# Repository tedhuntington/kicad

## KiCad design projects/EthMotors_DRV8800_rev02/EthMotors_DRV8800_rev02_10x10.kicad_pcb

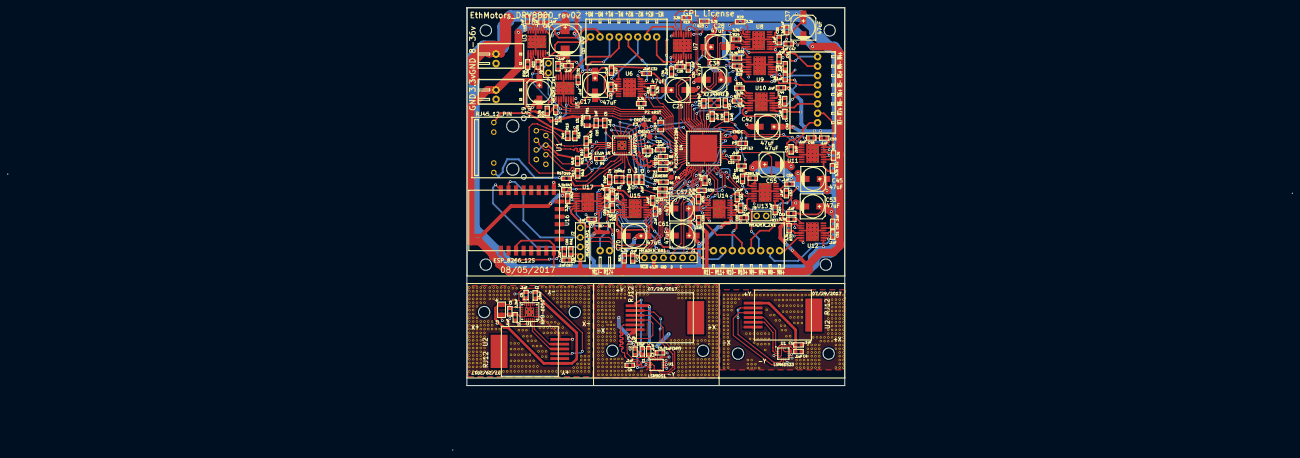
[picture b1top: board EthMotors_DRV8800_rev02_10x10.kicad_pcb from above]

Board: 2 copper layers, 100.0 x 100.0 mm, 178 parts (0 on the bottom side), 169 nets.

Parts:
C1, C1#4, C2#3, C3#3, C4#2, C4#3, C4#4, C5, C5#2, C6, C7, C8, C10, C11, C12, C16, C18, C21, C22, C23, C24, C26, C27, C29, C30, C31, C32, C33, C34, C35, C36, C39, C40, C41, C43, C44, C46, C47, C48, C49, C50, C51, C52, C54, C56, C58, C59, C60, C62, C63, C64, C65, C66, C67, C68, C69, C71, C72: .1uF; TED_SM0603_C
C1#2: 10nF; TED_SM0603_C
C1#3: 10uF; TED_SM0603_C
C2, C15: 1uF; TED_SM0603_C
C2#2: 2.2nF; TED_SM0603_C
C3, C4: 10pF; TED_SM0603_C
C3#2: 4.7uF; TED_SM3216_1206_ELEC_C
C5#3: .01uF(16V); TED_SM0603_C
C9, C17, C25, C28, C37, C38, C42, C45, C53, C55, C57, C61, C70: 47uF; c_elec_6.3x7.7
C13: 47uF; TED_c_elec_8x10
C14: 10uF (low ESR 1ohm); TED_SM0805_C
C19, C20: 9pF; TED_SM0603_C
FB1: 500mA; TED_SM0805_C
H1, H1#2, H1#3, H1#4, H2, H2#2, H2#3, H2#4, H3, H4: HOLE; TED_Hole_3mm
J1: HEADER_6X1; TED_HEADER_6x1
J2: HEADER_4X1; TED_HEADER_4x1
J3, J10: Logic DC_2.1MM; TED_TERMINAL_SPRING_2.54MM_2PIN_1989748
J4, J5, J7: TERMINAL_8X1; TED_TERMINAL_SPRING_2.54MM_8PIN_1989803
J6: Terminal_2x1; TED_TERMINAL_SPRING_2.54MM_2PIN_1989748
J8, J9: HEADER_2X1; TED_HEADER_2x1
P1: EMDIO; TED_TEST_PAD
P2: nRST; TED_TEST_PAD
P3: EREFCLK; TED_TEST_PAD
P4: ERXERR; TED_TEST_PAD
P5: EMDC; TED_TEST_PAD
R1, R2, R3, R6, R7, R8: 33; TED_SM0603_R
R4: 12.1k 1%; TED_SM0603_R
R5: 10; TED_SM0603_R
R9, R10, R11, R12: 49.9; TED_SM0603_R
R13, R15: 249; TED_SM0603_R
R14: 4.7k; TED_SM0603_R
R16: 10k 1%; TED_SM0603_R
R17, R18, R19, R20, R21, R22, R23, R24, R25, R26, R27, R28, R29, R30, R31, R32, R33, R34, R35, R36, R37, R38, R39, R40, R42, R43: 3.3k; TED_SM0603_R
R41: 10k; TED_SM0603_R
U1: RJ45_12_PIN; TED_RJ45_12pin
U1#2: MPU-6050; TED_QFN24+1_NO_PASTE
U1#3: LSM9DS1; LGA-24
U1#4: LSM6DS33; LGA-16
U2: LAN8720A; TED_QFN24+1
U2#2, U2#3, U2#4: RJ12; TED_RJ12_855135002
U3, U5, U6, U7, U8, U9, U10, U11, U12, U13, U14, U15, U17: DRV8800_PWP; TSSOP_16+1H
U4: PIC32MX664F128H; TED_QFN64+1
U16: ESP_8266_12S
X1: 25Mhz; TED_crystal_FA-20H
X2: 24MHz; crystal_TSX3225

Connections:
AVDD: C5.1, C15.1, FB1.2, R9.1, R10.1, R11.1, R12.1, U1.4, U1.5, U2.1, U2.19
ECRSDV: R8.2, U4.62
EMDC: P5.1, U2.13, U4.30
EMDIO: P1.1, U2.12, U4.49
EREFCLK: P3.1, U2.14, U4.63
ERXD0: R7.2, U4.61
ERXD1: R6.2, U4.60
ERXERR: P4.1, U2.10, U4.64
ETXD0: R2.2, U4.2
ETXD1: R3.2, U4.3
ETXEN: R1.2, U4.1
GND: C1.2, C1#2.2, C1#3.2, C1#4.2, C2.2, C2#2.2, C2#3.2, C3.2, C3#2.2, C3#3.2, C4.1, C4#2.2, C4#3.2, C4#4.2, C5.2, C5#2.2, C5#3.2, C7.2, C8.2, C9.2, C10.2, C11.2, C12.2, C13.2, C14.2, C15.2, C16.2, C17.2, C18.2, C19.2, C20.2, C21.2, C24.2, C25.2, C28.2, C31.2, C32.2, C34.2, C37.2, C38.2, C42.2, C45.2, C47.2, C48.2, C49.2, C50.2, C53.2, C55.2, C57.2, C61.2, C63.2, C64.2, C65.2, C66.2, C67.2, C68.2, C70.2, C72.2, J1.3, J2.4, J3.2, J9.1, J9.2, J10.2, R4.2, R16.2, U1.8, U1.10, U1.11, U1#2.1, U1#2.9, U1#2.11, U1#2.18, U1#2.25, U1#3.5, U1#3.6, U1#3.14, U1#3.15, U1#3.16, U1#3.17, U1#3.18, U1#3.19, U1#3.20, U1#4.4, U1#4.8, U1#4.9, U1#4.10, U1#4.11, U1#4.12, U1#4.13, U1#4.15, U2.25, U2#2.1, U2#3.1, U2#4.1, U3.4, U3.8, U3.13, U3.17, U4.9, U4.20, U4.25, U4.41, U4.65, U5.4, U5.8, U5.13, U5.17, U6.4, U6.8, U6.13, U6.17, U7.4, U7.8, U7.13, U7.17, U8.4, U8.8, U8.13, U8.17, U9.4, U9.8, U9.13, U9.17, U10.4, U10.8, U10.13, U10.17, U11.4, U11.8, U11.13, U11.17, U12.4, U12.8, U12.13, U12.17, U13.4, U13.8, U13.13, U13.17, U14.4, U14.8, U14.13, U14.17, U15.4, U15.8, U15.13, U15.17, U16.15, U17.4, U17.8, U17.13, U17.17, X1.2, X1.4, X2.2, X2.4
GreenLED: R15.1, U1.9
INT: U1#2.12, U2#2.4
INT1: U1#3.11, U1#4.7, U2#3.4, U2#4.4
INT2: U1#3.12, U1#4.6, U2#3.5, U2#4.5
M0+: J7.8, U3.7
M0-: J7.7, U3.10
M1+: J7.6, U5.7
M1-: J7.5, U5.10
M2+: J7.4, U6.7
M2-: J7.3, U6.10
M3+: J7.2, U7.7
M3-: J7.1, U7.10
M4+: J4.8, U8.7
M4-: J4.7, U8.10
M5+: J4.6, U9.7
M5-: J4.5, U9.10
M6+: J4.4, U10.7
M6-: J4.3, U10.10
M7+: J4.2, U11.7
M7-: J4.1, U11.10
M8+: J5.8, U12.7
M8-: J5.7, U12.10
M9+: J5.6, U13.7
M9-: J5.5, U13.10
M10+: J5.4, U14.7
M10-: J5.3, U14.10
M11+: J5.2, U15.7
M11-: J5.1, U15.10
M12+: J6.2, U17.7
M12-: J6.1, U17.10
unnamed: C1.1, C2.1, U2.6
unnamed: C2#2.1, C2#3.1, U1#2.20, U1#3.24
unnamed: C3.1, U2.5, X1.1
unnamed: C4#2.1, U1#2.10
unnamed: C4.2, U2.4, X1.3
unnamed: C5#3.1, U1#3.21
unnamed: C6.1, U5.12
unnamed: C6.2, U5.11
unnamed: C10.1, R5.2, U4.19
unnamed: C14.1, U4.56
unnamed: C19.1, U4.40, X2.1
unnamed: C20.1, U4.39, X2.3
unnamed: C22.1, U6.12
unnamed: C22.2, U6.11
unnamed: C23.2, U5.14
unnamed: C26.1, U7.12
unnamed: C26.2, U7.11
unnamed: C27.2, U6.14
unnamed: C29.1, U3.12
unnamed: C29.2, U3.11
unnamed: C30.2, U7.14
unnamed: C33.2, U3.14
unnamed: C35.1, U8.12
unnamed: C35.2, U8.11
unnamed: C36.1, U9.12
unnamed: C36.2, U9.11
unnamed: C39.1, U10.12
unnamed: C39.2, U10.11
unnamed: C40.2, U8.14
unnamed: C41.2, U9.14
unnamed: C43.1, U11.12
unnamed: C43.2, U11.11
unnamed: C44.2, U10.14
unnamed: C46.2, U11.14
unnamed: C51.1, U12.12
unnamed: C51.2, U12.11
unnamed: C52.1, U13.12
unnamed: C52.2, U13.11
unnamed: C54.1, U14.12
unnamed: C54.2, U14.11
unnamed: C56.2, U12.14
unnamed: C58.1, U15.12
unnamed: C58.2, U15.11
unnamed: C59.2, U13.14
unnamed: C60.2, U14.14
unnamed: C62.2, U15.14
unnamed: C68.1, R41.2, U16.1
unnamed: C69.1, U17.12
unnamed: C69.2, U17.11
unnamed: C71.2, U17.14
unnamed: R1.1, U2.16
unnamed: R2.1, U2.17
unnamed: R3.1, U2.18
unnamed: R4.1, U2.24
unnamed: R6.1, U2.7
unnamed: R7.1, U2.8
unnamed: R8.1, U2.11
unnamed: R13.2, U2.3
unnamed: R15.2, R16.1, U2.2
unnamed: R17.2, U5.5
unnamed: R18.2, U6.5
unnamed: R19.2, U7.5
unnamed: R20.2, U5.1
unnamed: R21.2, U6.1
unnamed: R22.2, U3.5
unnamed: R23.2, U7.1
unnamed: R24.2, U8.5
unnamed: R25.2, U9.5
unnamed: R26.2, U3.1
unnamed: R27.2, U10.5
unnamed: R28.2, U11.5
unnamed: R29.2, U8.1
unnamed: R30.2, U9.1
unnamed: R31.2, U10.1
unnamed: R32.2, U11.1
unnamed: R33.2, U12.5
unnamed: R34.2, U13.5
unnamed: R35.2, U14.5
unnamed: R36.2, U15.5
unnamed: R37.2, U12.1
unnamed: R38.2, U13.1
unnamed: R39.2, U14.1
unnamed: R40.2, U15.1
unnamed: R42.2, U17.5
unnamed: R43.2, U17.1
unnamed: U1.7, U1#2.7
unnamed: U1#2.14, U1#4.14
PGEC1_RB1: J1.5, U4.15, U13.3
PGED1_RB0: J1.4, U4.16, U12.6
RB2: U4.14, U13.6
RB4: U4.12, U14.3
RB5: U4.11, U14.6
RC13: U4.47, U8.3
RC14: U4.48, U7.6
RD0: U4.46, U8.6
RD2: U4.50, U7.3
RD3: U4.51, U6.6
RD4: U4.52, U6.3
RD5: U4.53, U5.6
RD6: U4.54, U5.3
RD7: J8.2, U3.6, U4.55
RD8: U4.42, U10.6
RD9: U4.43, U10.3
RD10: U4.44, U9.6
RD11: U4.45, U9.3
RF1: J8.1, U3.3, U4.59
RF3: U4.33, U11.3
RF4: U4.31, U12.3
RF5: U4.32, U11.6
RG6: U4.4, U17.6
RG7: U4.5, U17.3
RG8: U4.6, U15.6
RG9: U4.8, U15.3
RXN: R12.2, U1.6, U2.22
RXP: R11.2, U1.3, U2.23
SCL: U1#2.23, U1#3.2, U1#4.2, U2#2.3, U2#3.3, U2#4.3
SDA: U1#2.24, U1#3.4, U1#4.3, U2#2.2, U2#3.2, U2#4.2
TXN: R10.2, U1.2, U2.20
TXP: R9.2, U1.1, U2.21
U5RX: J2.2, U4.21, U16.22
U5TX: J2.3, U4.29, U16.21
VDD: C8.1, C9.1, C11.1, C12.1, C16.1, C18.1, C21.1, C67.1, FB1.1, J1.2, J2.1, J3.1, R5.1, R14.1, R17.1, R18.1, R19.1, R20.1, R21.1, R22.1, R23.1, R24.1, R25.1, R26.1, R27.1, R28.1, R29.1, R30.1, R31.1, R32.1, R33.1, R34.1, R35.1, R36.1, R37.1, R38.1, R39.1, R40.1, R41.1, R42.1, R43.1, U2.9, U3.2, U4.10, U4.26, U4.35, U4.38, U4.57, U5.2, U6.2, U7.2, U8.2, U9.2, U10.2, U11.2, U12.2, U13.2, U14.2, U15.2, U16.3, U16.8, U17.2
VMotor: C13.1, C17.1, C23.1, C24.1, C25.1, C27.1, C28.1, C30.1, C31.1, C32.1, C33.1, C34.1, C37.1, C38.1, C40.1, C41.1, C42.1, C44.1, C45.1, C46.1, C47.1, C48.1, C49.1, C50.1, C53.1, C55.1, C56.1, C57.1, C59.1, C60.1, C61.1, C62.1, C63.1, C64.1, C65.1, C66.1, C70.1, C71.1, C72.1, J10.1, U3.9, U5.9, U6.9, U7.9, U8.9, U9.9, U10.9, U11.9, U12.9, U13.9, U14.9, U15.9, U17.9
Vdd: C1#2.1, C1#3.1, C1#4.1, C3#2.1, C3#3.1, C4#3.1, C4#4.1, C5#2.1, U1#2.8, U1#2.13, U1#3.1, U1#3.3, U1#3.7, U1#3.8, U1#3.22, U1#3.23, U1#4.1, U1#4.5, U1#4.16, U2#2.6, U2#3.6, U2#4.6
YellowLED: R13.1, U1.12
nRST: P2.1, U2.15, U4.58
~MCLR~: C7.1, J1.1, R14.2, U4.7

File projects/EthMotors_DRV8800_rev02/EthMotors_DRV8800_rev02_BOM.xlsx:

/home/ted/kicad/projects/EthMotors_DRV8800_rev01/EthMotors_DRV8800_rev01.sch
Sun 12 Oct 2014 08:54:45 PM PDT
eeschema (2013-08-24 BZR 4298)-stable
Component Count:147
Ref | Qnty | Value | Part | Part# | Unit Cost | Total Cost | Major Distributor | Minor Distributor
C11, C21, C12, C8, C16, C5, C18, C10, C1, C7, C29, C33, C24, C30, C34, C26, C31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 | 46 | .1uF | ted_capacitors/C(SMALL) | Vj0603V104ZXAPW1BC | 0.1 | 4.6000000000000005 | Mouser
C13, C17, C22, C6, C37, C38, C39, C36, C53, C54, C55, C52, | 12 | 100uF | ted_capacitors/C_POL_SMALL | UWT1H101MNL 1GS | 0.44 | 5.28 | Mouser
C14, | 1 | 10uF (low ESR 1ohm) | ted_capacitors/C(SMALL) | LMK212F106ZG-T | 0.18 | 0.18 | Mouser
C19, C20, | 2 | 9pF | ted_capacitors/C(SMALL) | GRM1885C1H9R0DA01D | 0.1 | 0.2 | Digi-Key/Mouser
C2, C15, | 2 | 1uF | ted_capacitors/C(SMALL) | GRM188R61E105KA12D | 0.1 | 0.2 | Digi-Key
C4, C3, | 2 | 10pF | ted_capacitors/C(SMALL) | GRM1885C1H100FA01J | 0.12 | 0.24 | Mouser
C9, | 1 | 4.7uF | ted_capacitors/C(SMALL) | C0603C475K9PACTU | 0.13 | 0.13 | Mouser
FB1, | 1 | 500mA | ted_inductors/FERRITE_BEAD | MPZ2012S601A | 0.12 | 0.12 | Mouser
H1, H2, H4, H3, | 4 | HOLE | TED_holes/HOLE |  | 0 | 0
J1, | 1 | HEADER_6X1 | ted_connectors/HEADER_6X1 | 640456-6 | 0.27 | 0.27 | Mouser
J2, | 1 | JUMPER_2X1 | ted_connectors/JUMPER_2X1 | FCI 68000-102HLF | 0.19 | 0.19 | Digi-Key | AliExpress/Ebay
J3, J10, | 2 | Logic DC_2.1MM | ted_connectors/DC_2.1MM | Switchcraft RASM722X | 1.1200000000000001 | 2.2400000000000002 | Digi-Key/Mouser | AliExpress/Ebay
J7, J4, J5, | 3 | TERMINAL_8X1 | ted_connectors/TERMINAL_8X1 | 1814760 | 1.31 | 3.93 | Mouser
R12, R11, R10, R9, | 4 | 49.9 | ted_resistors/R_SMALL | ERJ-3EKF49R9V | 0.1 | 0.4 | Digi-Key
R14, | 1 | 4.7k | ted_resistors/R_SMALL | ERJ-3EKF4701V | 0.1 | 0.1 | Digi-Key
R15, R13, | 2 | 249 | ted_resistors/R_SMALL | ERJ-2RKF2490X | 0.1 | 0.2 | Digi-Key/Mouser
R16, | 1 | 10k 1% | ted_resistors/R_SMALL | ERJ-3EKF1001V | 0.1 | 0.1 | Digi-Key
R18, R19, R20, R17, R30, R31, R32, R29, R42, R43, R44, R41, | 12 | 10m | ted_resistors/R_SMALL | RL1220S-R10-F | 0.32 | 3.84 | Digi-Key
R26, R22, R27, R23, R28, R24, R25, R21, R38, R34, R39, R35, R40, R36, R37, R33,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 | 24 | 3.3k | ted_resistors/R_SMALL | ERJ-3EKF3301V | 0.1 | 2.4000000000000004 | Digi-Key
R4, | 1 | 12.1k 1% | ted_resistors/R_SMALL | ERJ-6ENF1212V | 0.1 | 0.1 | Mouser
R5, | 1 | 10 | ted_resistors/R_SMALL | CRCW060310R0FKEA | 0.1 | 0.1 | Digi-Key/Mouser
R7, R6, R2, R1, R3, R8, | 6 | 33 | ted_resistors/R_SMALL | RC0603FR-0733RL | 0.1 | 0.60000000000000009 | Digi-Key/Mouser
U1, | 1 | RJ45_12_PIN_SMD | ted_connectors/RJ45_12_PIN_SMD | HR961160C | 2.56 | 2.56 |  | AliExpress
U2, | 1 | LAN8720A | ted_ic/LAN8720A | LAN8720A | 1.49 | 1.49 | Digi-Key
U4, | 1 | PIC32MX664F128H | ted_ic/PIC32MX664F128H | PIC32MX664F128H-I/MR | 4.78 | 4.78 | MicrosoftDirect
U5, U6, U7, U3, U9, U10, U11, U8, U13, U14, U15, U12, | 12 | DRV8800_RTY | ted_ic/DRV8800_RTY | DRV8800RTYR | 2.38 | 28.56 | TI Store
X1, | 1 | 25Mhz | ted_crystals/CRYSTAL_W_2GND | FA-20H 25.0000MF20X-K3 | 0.73 | 0.73 | Mouser
X2, | 1 | 24MHz | ted_crystals/CRYSTAL_W_2GND | TSX-3225 24.0000MF20G-AC3 | 0.51 | 0.51 | Mouser
 |  |  |  |  |  | 64.05

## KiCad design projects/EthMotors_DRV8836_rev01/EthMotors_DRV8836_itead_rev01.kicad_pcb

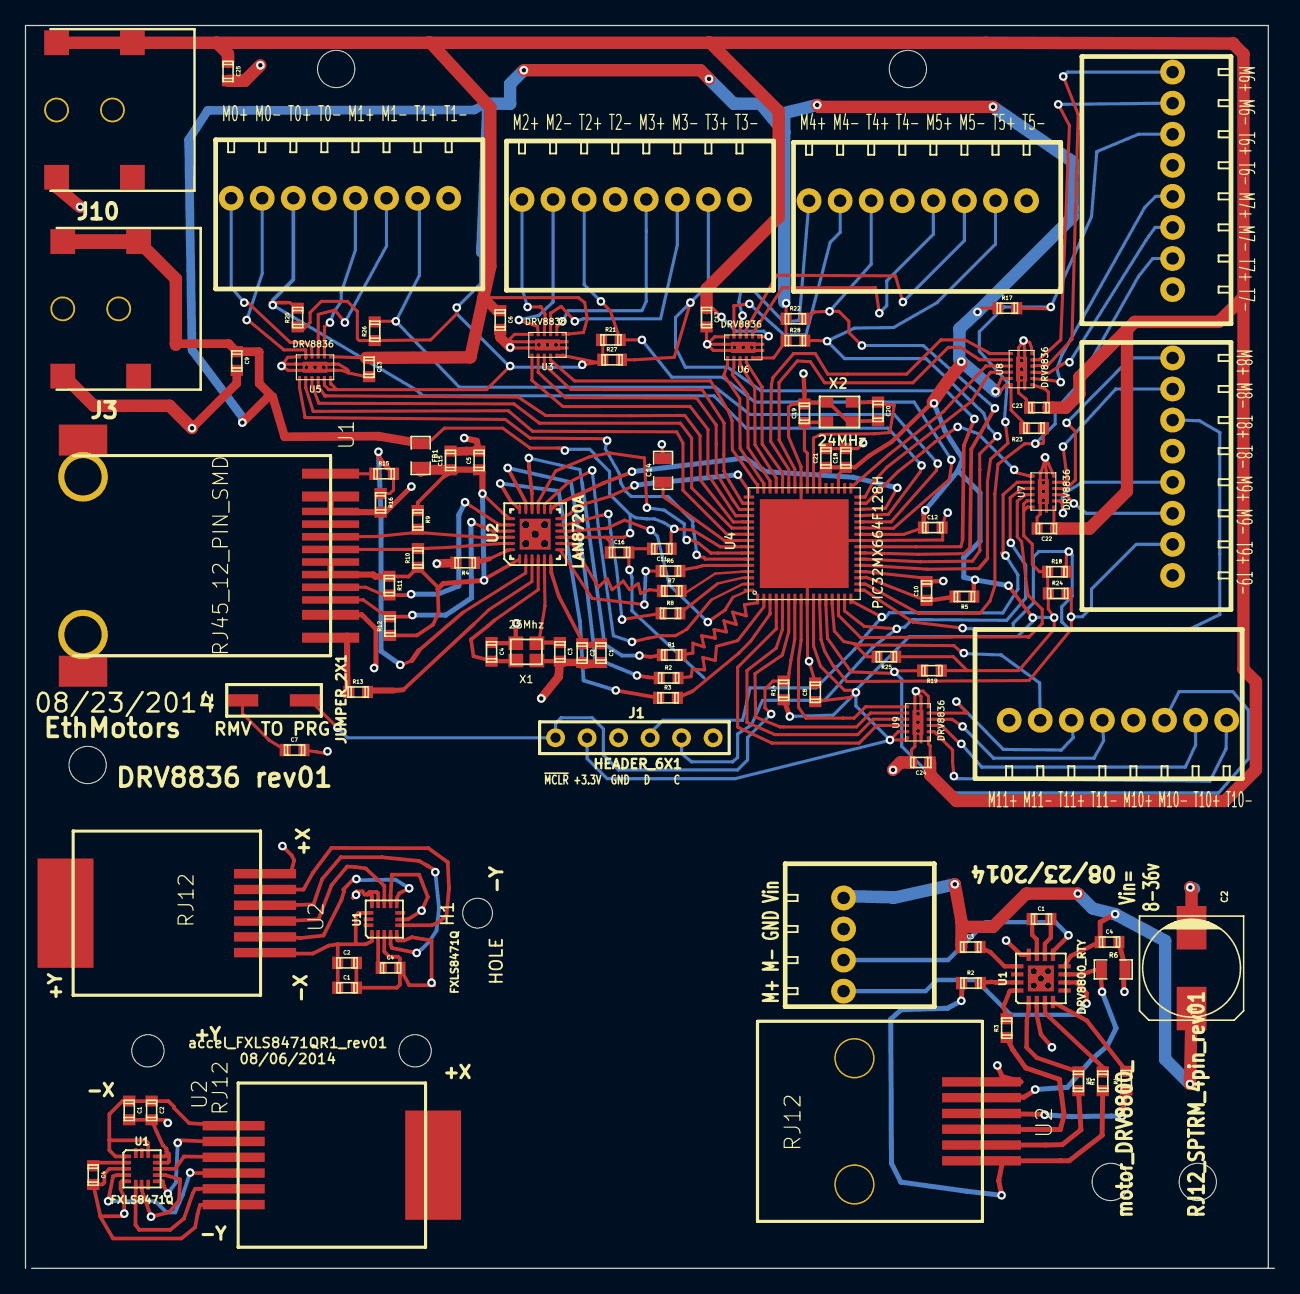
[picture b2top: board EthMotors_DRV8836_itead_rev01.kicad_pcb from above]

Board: 2 copper layers, 100.5 x 100.0 mm, 106 parts (0 on the bottom side), 121 nets.

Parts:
C1, C2#2, C2#4, C4#2, C4#4, C5, C6, C7, C8, C10, C11, C12, C13, C16, C17, C18, C21, C22, C23, C24: .1uF; TED_SM0603
C1#2, C1#4, C2, C15: 1uF; TED_SM0603
C1#3, C3#2: .1uF (50v); TED_SM0603
C2#3: 100uF 50v; TED_c_elec_8x10
C3, C4: 10pF; TED_SM0603
C4#3: .1uF 50v; TED_SM0603
C9, C25: 4.7uF; TED_SM0603
C14: 10uF (low ESR 1ohm); TED_SM0805
C19, C20: 9pF; TED_SM0603
FB1: 500mA; TED_SM0805
H1, H1#3, H2, H2#2, H4: HOLE; TED_Hole_3mm
H1#2: HOLE; TED_Hole_2_4mm
H1#4, H2#3: HOLE; TED_Hole_2_6mm
J1: HEADER_6X1; TED_HEADER_6x1
J1#2: TERMINAL_4X1; TED_TERMINAL_SPRING_2.54MM_4PIN_1989764
J2: JUMPER_2X1; TED_HEADER_2x1_SMT
J3, J10: Logic DC_2.1MM; TED_DC_2.1mm_SMT
J4, J5, J6, J7, J8, J9: TERMINAL_8X1; TED_TERMINAL_SPRING_2.54MM_8PIN_1989803
R1, R2, R3, R6, R7, R8: 33; TED_SM0603
R1#2, R2#2: 3.3k; TED_SM0603
R3#2, R4#2, R5#2, R17, R18, R19, R20, R21, R22, R23, R24, R25, R26, R27, R28: 1k; TED_SM0603
R4: 12.1k 1%; TED_SM0603
R5: 10; TED_SM0603
R6#2: 10m; TED_SM0805
R9, R10, R11, R12: 49.9; TED_SM0603
R13, R15: 249; TED_SM0603
R14: 4.7k; TED_SM0603
R16: 10k 1%; TED_SM0603
U1: RJ45_12_PIN_SMD; TED_RJ45_12pin_SMD
U1#2, U1#4: FXLS8471Q; TED_QFN16_3x5
U1#3: DRV8800_RTY; TED_QFN16+1
U2: LAN8720A; TED_QFN24
U2#2, U2#4: RJ12; TED_RJ12_855135002
U2#3: RJ12; TED_RJ12_955016669
U3, U5, U6, U7, U8, U9: DRV8836; TED_WSON-12
U4: PIC32MX664F128H; TED_QFN64+1
X1: 25Mhz; TED_crystal_FA-20H
X2: 24MHz; TED_crystal_TSX3225

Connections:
+3.3v: C8.1, C9.1, C11.1, C12.1, C16.1, C18.1, C21.1, FB1.1, J1.2, J3.1, R5.1, R14.1, R17.1, R18.1, R19.1, R20.1, R21.1, R22.1, R23.1, R24.1, R25.1, R26.1, R27.1, R28.1, U2.9, U3.11, U3.12, U4.10, U4.26, U4.35, U4.38, U4.57, U5.11, U5.12, U6.11, U6.12, U7.11, U7.12, U8.11, U8.12, U9.11, U9.12
AVDD: C5.1, C15.1, FB1.2, R9.1, R10.1, R11.1, R12.1, U1.5, U1.6, U2.1, U2.19
CS: R6#2.1, U1#3.7, U2#3.2
ECRSDV: R8.2, U4.62
EMDC: U2.13, U4.30
EMDIO: U2.12, U4.49
EREFCLK: U2.14, U4.63
ERXD0: R7.2, U4.61
ERXD1: R6.2, U4.60
ERXERR: U2.10, U4.64
ETXD0: R2.2, U4.2
ETXD1: R3.2, U4.3
ETXEN: R1.2, U4.1
GND: C1.2, C1#2.2, C1#4.2, C2.2, C2#2.2, C2#3.2, C2#4.2, C3.2, C4.1, C4#2.2, C4#3.2, C4#4.2, C5.2, C6.2, C7.2, C8.2, C9.2, C10.2, C11.2, C12.2, C13.2, C14.2, C15.2, C16.2, C17.2, C18.2, C19.2, C20.2, C21.2, C22.2, C23.2, C24.2, C25.2, J1.3, J1#2.2, J3.2, J4.1, J4.5, J5.1, J5.5, J6.1, J6.5, J7.1, J7.5, J8.1, J8.5, J9.1, J9.5, J10.2, R4.2, R6#2.2, R16.2, U1.2, U1.10, U1.11, U1#2.3, U1#2.5, U1#2.7, U1#2.10, U1#2.12, U1#2.13, U1#3.2, U1#3.12, U1#3.17, U1#4.3, U1#4.5, U1#4.7, U1#4.10, U1#4.12, U1#4.13, U2.25, U2#2.1, U2#3.1, U2#4.1, U3.6, U3.PP, U4.9, U4.20, U4.25, U4.41, U4.65, U5.6, U5.PP, U6.6, U6.PP, U7.6, U7.PP, U8.6, U8.PP, U9.6, U9.PP, X1.2, X1.4, X2.2, X2.4
GreenLED: R15.1, U1.12
INT1: U1#2.11, U1#4.11, U2#2.4, U2#4.4
INT2: U1#2.9, U1#4.9, U2#2.5, U2#4.5
M0+: J7.8, U5.4
M0-: J7.7, U5.5
M1+: J7.4, U5.2
M1-: J7.3, U5.3
M2+: J8.8, U3.4
M2-: J8.7, U3.5
M3+: J8.4, U3.2
M3-: J8.3, U3.3
M4+: J9.8, U6.4
M4-: J9.7, U6.5
M5+: J9.4, U6.2
M5-: J9.3, U6.3
M6+: J4.8, U8.4
M6-: J4.7, U8.5
M7+: J4.4, U8.2
M7-: J4.3, U8.3
M8+: J5.8, U7.4
M8-: J5.7, U7.5
M9+: J5.4, U7.2
M9-: J5.3, U7.3
M10+: J6.8, U9.2
M10-: J6.7, U9.3
M11+: J6.4, U9.4
M11-: J6.3, U9.5
MODE: R3#2.2, U1#3.16
Motor1OutA: J1#2.4, U1#3.6
Motor1OutB: J1#2.3, U1#3.9
unnamed: C1#3.1, U1#3.11
unnamed: C1#3.2, U1#3.10
unnamed: R2#2.2, U1#3.15
unnamed: R1#2.2, U1#3.3
unnamed: C4#2.1, C4#4.1, U1#2.2, U1#4.2
unnamed: R5#2.2, U2#3.5
unnamed: R4#2.1, U2#3.3
unnamed: R3#2.1, U2#3.4
unnamed: C3#2.2, U1#3.13
unnamed: R8.1, U2.11
unnamed: R3.1, U2.18
unnamed: R2.1, U2.17
unnamed: R1.1, U2.16
unnamed: R13.2, U2.3
unnamed: R15.2, R16.1, U2.2
unnamed: R4.1, U2.24
unnamed: R7.1, U2.8
unnamed: R6.1, U2.7
unnamed: C1.1, C2.1, U2.6
unnamed: C7.1, J2.1
unnamed: C4.2, U2.4, X1.3
unnamed: C3.1, U2.5, X1.1
unnamed: C10.1, R5.2, U4.19
unnamed: C19.1, U4.40, X2.1
unnamed: C20.1, U4.39, X2.3
PGEC1_RB1: J1.5, U4.15, U7.9
PGED1_RB0: J1.4, U4.16, U7.8
PHASE: R5#2.1, U1#3.1
PWM: R4#2.2, U1#3.4
RB2: U4.14, U7.10
RB3: J6.2, R25.2, U4.13
RB4: J6.6, R19.2, U4.12
RB5: J5.2, R24.2, U4.11
RB6: J5.6, R18.2, U4.17
RB7: J4.2, R23.2, U4.18
RB8: J4.6, R17.2, U4.21
RB9: J9.2, R28.2, U4.22
RB10: J9.6, R22.2, U4.23
RB11: J8.2, R27.2, U4.24
RB12: J8.6, R21.2, U4.27
RB13: J7.2, R26.2, U4.28
RB14: J7.6, R20.2, U4.29
RC13: U4.47, U6.7
RC14: U3.10, U4.48
RD0: U4.46, U6.8
RD2: U3.9, U4.50
RD3: U3.8, U4.51
RD4: U3.7, U4.52
RD5: U4.53, U5.10
RD6: U4.54, U5.9
RD7: U4.55, U5.8
RD8: U4.42, U8.8
RD9: U4.43, U8.7
RD10: U4.44, U6.10
RD11: U4.45, U6.9
RF1: U4.59, U5.7
RF3: U4.33, U8.9
RF4: U4.31, U7.7
RF5: U4.32, U8.10
RG6: U4.4, U9.10
RG7: U4.5, U9.9
RG8: U4.6, U9.8
RG9: U4.8, U9.7
RXN: R9.2, U1.8, U2.22
RXP: R10.2, U1.7, U2.23
SCL: U1#2.4, U1#4.4, U2#2.3, U2#4.3
SDA: U1#2.6, U1#4.6, U2#2.2, U2#4.2
TXN: R11.2, U1.4, U2.20
TXP: R12.2, U1.3, U2.21
VCAP: C14.1, U4.56
VDD: R1#2.1, R2#2.1, U2#3.6
VMotor: C6.1, C13.1, C17.1, C22.1, C23.1, C24.1, C25.1, J10.1, U3.1, U5.1, U6.1, U7.1, U8.1, U9.1
Vdd: C1#2.1, C1#4.1, C2#2.1, C2#4.1, U1#2.1, U1#2.14, U1#4.1, U1#4.14, U2#2.6, U2#4.6
Vin: C2#3.1, C3#2.1, C4#3.1, J1#2.1, U1#3.8
YellowLED: R13.1, U1.1
nRST: U2.15, U4.58
~MCLR~: J1.1, J2.2, R14.2, U4.7

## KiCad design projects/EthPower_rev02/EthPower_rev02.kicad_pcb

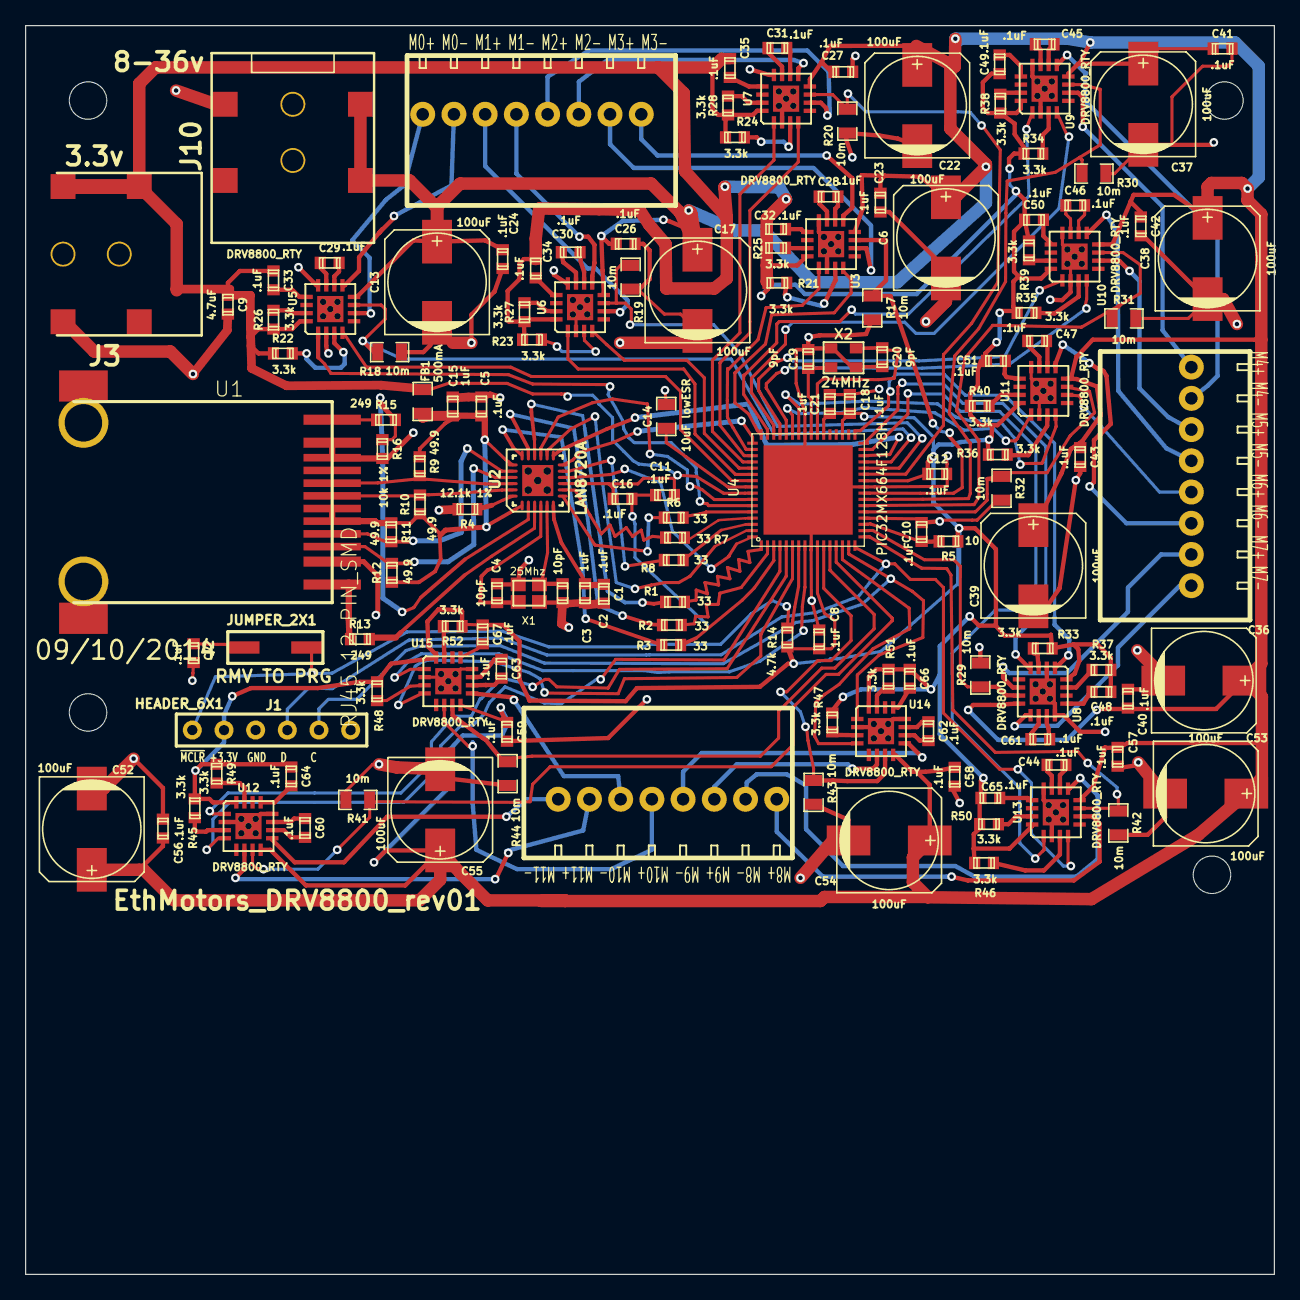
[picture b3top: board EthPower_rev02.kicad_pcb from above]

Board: 2 copper layers, 100.0 x 100.0 mm, 147 parts (0 on the bottom side), 159 nets.

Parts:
C1, C5, C7, C8, C10, C11, C12, C16, C18, C21, C23, C24, C26, C27, C28, C29, C30, C31, C32, C33, C34, C35, C40, C41, C42, C43, C44, C45, C46, C47, C48, C49, C50, C51, C56, C57, C58, C59, C60, C61, C62, C63, C64, C65, C66, C67: .1uF; TED_SM0603_C
C2, C15: 1uF; TED_SM0603_C
C3, C4: 10pF; TED_SM0603_C
C6, C13, C17, C22, C36, C37, C38, C39, C52, C53, C54, C55: 100uF; TED_c_elec_8x10
C9: 4.7uF; TED_SM0603_C
C14: 10uF lowESR; TED_SM0805_C
C19, C20: 9pF; TED_SM0603_C
FB1: 500mA; TED_SM0805_R
H1, H2, H3, H4: HOLE; TED_Hole_3mm
J1: HEADER_6X1; TED_HEADER_6x1
J2: JUMPER_2X1; TED_HEADER_2x1_SMT
J3, J10: Logic DC_2.1MM; TED_DC_2.1mm_SMT
J4, J5, J7: TERMINAL_8X1; TED_TERMINAL_SPRING_2.54MM_8PIN_1989803
R1, R2, R3, R6, R7, R8: 33; TED_SM0603_R
R4: 12.1k 1%; TED_SM0603_R
R5: 10; TED_SM0603_R
R9, R10, R11, R12: 49.9; TED_SM0603_R
R13, R15: 249; TED_SM0603_R
R14: 4.7k; TED_SM0603_R
R16: 10k 1%; TED_SM0603_R
R17, R18, R19, R20, R29, R30, R31, R32, R41, R42, R43, R44: 10m; TED_SM0805_R
R21, R22, R23, R24, R25, R26, R27, R28, R33, R34, R35, R36, R37, R38, R39, R40, R45, R46, R47, R48, R49, R50, R51, R52: 3.3k; TED_SM0603_R
U1: RJ45_12_PIN_SMD; TED_RJ45_12pin_SMD
U2: LAN8720A; TED_QFN24
U3, U5, U6, U7, U8, U9, U10, U11, U12, U13, U14, U15: DRV8800_RTY; TED_QFN16+1
U4: PIC32MX664F128H; TED_QFN64+1
X1: 25Mhz; TED_crystal_FA-20H
X2: 24MHz; TED_crystal_TSX3225

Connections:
AVDD: C5.1, C15.1, FB1.2, R9.1, R10.1, R11.1, R12.1, U1.5, U1.6, U2.1, U2.19
ECRSDV: R8.2, U4.62
EMDC: U2.13, U4.30
EMDIO: U2.12, U4.49
EREFCLK: U2.14, U4.63
ERXD0: R7.2, U4.61
ERXD1: R6.2, U4.60
ERXERR: U2.10, U4.64
ETXD0: R2.2, U4.2
ETXD1: R3.2, U4.3
ETXEN: R1.2, U4.1
GND: C1.2, C2.2, C3.2, C4.1, C5.2, C6.2, C7.2, C8.2, C9.2, C10.2, C11.2, C12.2, C13.2, C14.2, C15.2, C16.2, C17.2, C18.2, C19.2, C20.2, C21.2, C22.2, C23.2, C24.2, C26.2, C27.2, C36.2, C37.2, C38.2, C39.2, C40.2, C41.2, C42.2, C43.2, C52.2, C53.2, C54.2, C55.2, C56.2, C57.2, C58.2, C59.2, J1.3, J3.2, J10.2, R4.2, R16.2, R17.2, R18.2, R19.2, R20.2, R29.2, R30.2, R31.2, R32.2, R41.2, R42.2, R43.2, R44.2, U1.2, U1.10, U1.11, U2.25, U3.2, U3.12, U3.17, U4.9, U4.20, U4.25, U4.41, U4.65, U5.2, U5.12, U5.17, U6.2, U6.12, U6.17, U7.2, U7.12, U7.17, U8.2, U8.12, U8.17, U9.2, U9.12, U9.17, U10.2, U10.12, U10.17, U11.2, U11.12, U11.17, U12.2, U12.12, U12.17, U13.2, U13.12, U13.17, U14.2, U14.12, U14.17, U15.2, U15.12, U15.17, X1.2, X1.4, X2.2, X2.4
GreenLED: R15.1, U1.12
M0+: J7.8, U5.6
M0-: J7.7, U5.9
M1+: J7.6, U6.6
M1-: J7.5, U6.9
M2+: J7.4, U7.6
M2-: J7.3, U7.9
M3+: J7.2, U3.6
M3-: J7.1, U3.9
M4+: J4.8, U9.6
M4-: J4.7, U9.9
M5+: J4.6, U10.6
M5-: J4.5, U10.9
M6+: J4.4, U11.6
M6-: J4.3, U11.9
M7+: J4.2, U8.6
M7-: J4.1, U8.9
M8+: J5.8, U13.6
M8-: J5.7, U13.9
M9+: J5.6, U14.6
M9-: J5.5, U14.9
M10+: J5.4, U15.6
M10-: J5.3, U15.9
M11+: J5.2, U12.6
M11-: J5.1, U12.9
unnamed: R8.1, U2.11
unnamed: R3.1, U2.18
unnamed: R2.1, U2.17
unnamed: R1.1, U2.16
unnamed: R4.1, U2.24
unnamed: R6.1, U2.7
unnamed: R7.1, U2.8
unnamed: C19.1, U4.40, X2.1
unnamed: C4.2, U2.4, X1.3
unnamed: C1.1, C2.1, U2.6
unnamed: C3.1, U2.5, X1.1
unnamed: C10.1, R5.2, U4.19
unnamed: C7.1, J2.1
unnamed: R13.2, U2.3
unnamed: R15.2, R16.1, U2.2
unnamed: C20.1, U4.39, X2.3
unnamed: C65.2, U13.13
unnamed: C61.1, U13.11
unnamed: C61.2, U13.10
unnamed: R50.2, U13.15
unnamed: R33.2, U8.3
unnamed: C62.1, U14.11
unnamed: C62.2, U14.10
unnamed: R46.2, U13.3
unnamed: C66.2, U14.13
unnamed: R40.2, U11.15
unnamed: C51.2, U11.13
unnamed: C47.1, U11.11
unnamed: C47.2, U11.10
unnamed: C44.2, U8.10
unnamed: C44.1, U8.11
unnamed: R37.2, U8.15
unnamed: C48.2, U8.13
unnamed: R36.2, U11.3
unnamed: C64.2, U12.13
unnamed: R49.2, U12.15
unnamed: C60.1, U12.11
unnamed: C60.2, U12.10
unnamed: R45.2, U12.3
unnamed: R47.2, U14.3
unnamed: R51.2, U14.15
unnamed: C67.2, U15.13
unnamed: R48.2, U15.3
unnamed: C63.1, U15.11
unnamed: C63.2, U15.10
unnamed: R52.2, U15.15
unnamed: R23.2, U6.3
unnamed: R27.2, U6.15
unnamed: C30.1, U6.11
unnamed: C30.2, U6.10
unnamed: C34.2, U6.13
unnamed: C35.2, U7.13
unnamed: R28.2, U7.15
unnamed: C31.2, U7.10
unnamed: C31.1, U7.11
unnamed: C33.2, U5.13
unnamed: C29.1, U5.11
unnamed: C29.2, U5.10
unnamed: R26.2, U5.15
unnamed: R22.2, U5.3
unnamed: R34.2, U9.3
unnamed: C46.1, U10.11
unnamed: C49.2, U9.13
unnamed: R38.2, U9.15
unnamed: R35.2, U10.3
unnamed: C46.2, U10.10
unnamed: R39.2, U10.15
unnamed: C50.2, U10.13
unnamed: C28.1, U3.11
unnamed: C28.2, U3.10
unnamed: C32.2, U3.13
unnamed: R25.2, U3.15
unnamed: R24.2, U7.3
unnamed: C45.2, U9.10
unnamed: C45.1, U9.11
unnamed: R21.2, U3.3
PGEC1_RB1: J1.5, U4.15, U14.1
PGED1_RB0: J1.4, U4.16, U13.4
RB2: U4.14, U14.4
RB3: R41.1, U4.13, U12.7
RB4: R44.1, U4.12, U15.7
RB5: R43.1, U4.11, U14.7
RB6: R42.1, U4.17, U13.7
RB7: R29.1, U4.18, U8.7
RB8: R32.1, U4.21, U11.7
RB9: R31.1, U4.22, U10.7
RB10: R30.1, U4.23, U9.7
RB11: R17.1, U3.7, U4.24
RB12: R20.1, U4.27, U7.7
RB13: R19.1, U4.28, U6.7
RB14: R18.1, U4.29, U5.7
RC13: U4.47, U9.1
RC14: U3.4, U4.48
RD0: U4.46, U9.4
RD2: U3.1, U4.50
RD3: U4.51, U7.4
RD4: U4.52, U7.1
RD5: U4.53, U6.4
RD6: U4.54, U6.1
RD7: U4.55, U5.4
RD8: U4.42, U11.4
RD9: U4.43, U11.1
RD10: U4.44, U10.4
RD11: U4.45, U10.1
RF1: U4.59, U5.1
RF3: U4.33, U8.1
RF4: U4.31, U13.1
RF5: U4.32, U8.4
RG6: U4.4, U12.4
RG7: U4.5, U12.1
RG8: U4.6, U15.4
RG9: U4.8, U15.1
RXN: R9.2, U1.8, U2.22
RXP: R10.2, U1.7, U2.23
TXN: R11.2, U1.4, U2.20
TXP: R12.2, U1.3, U2.21
VCAP: C14.1, U4.56
VDD: C8.1, C9.1, C11.1, C12.1, C16.1, C18.1, C21.1, C32.1, C33.1, C34.1, C35.1, C48.1, C49.1, C50.1, C51.1, C64.1, C65.1, C66.1, C67.1, FB1.1, J1.2, J3.1, R5.1, R14.1, R21.1, R22.1, R23.1, R24.1, R25.1, R26.1, R27.1, R28.1, R33.1, R34.1, R35.1, R36.1, R37.1, R38.1, R39.1, R40.1, R45.1, R46.1, R47.1, R48.1, R49.1, R50.1, R51.1, R52.1, U2.9, U3.16, U4.10, U4.26, U4.35, U4.38, U4.57, U5.16, U6.16, U7.16, U8.16, U9.16, U10.16, U11.16, U12.16, U13.16, U14.16, U15.16
VMotor: C6.1, C13.1, C17.1, C22.1, C23.1, C24.1, C26.1, C27.1, C36.1, C37.1, C38.1, C39.1, C40.1, C41.1, C42.1, C43.1, C52.1, C53.1, C54.1, C55.1, C56.1, C57.1, C58.1, C59.1, J10.1, U3.8, U5.8, U6.8, U7.8, U8.8, U9.8, U10.8, U11.8, U12.8, U13.8, U14.8, U15.8
YellowLED: R13.1, U1.1
nRST: U2.15, U4.58
~MCLR~: J1.1, J2.2, R14.2, U4.7

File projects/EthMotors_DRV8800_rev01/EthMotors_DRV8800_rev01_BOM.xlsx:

/home/ted/kicad/projects/EthMotors_DRV8800_rev01/EthMotors_DRV8800_rev01.sch
Sun 12 Oct 2014 08:54:45 PM PDT
eeschema (2013-08-24 BZR 4298)-stable
Component Count:147
Ref | Qnty | Value | Part | Part# | Unit Cost | Total Cost | Major Distributor | Minor Distributor
C11, C21, C12, C8, C16, C5, C18, C10, C1, C7, C29, C33, C24, C30, C34, C26, C31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 | 46 | .1uF | ted_capacitors/C(SMALL) | Vj0603V104ZXAPW1BC | 0.1 | 4.6 | Mouser
C13, C17, C22, C6, C37, C38, C39, C36, C53, C54, C55, C52, | 12 | 100uF | ted_capacitors/C_POL_SMALL | UWT1H101MNL 1GS | 0.44 | 5.28 | Mouser
C14, | 1 | 10uF (low ESR 1ohm) | ted_capacitors/C(SMALL) | LMK212F106ZG-T | 0.18 | 0.18 | Mouser
C19, C20, | 2 | 9pF | ted_capacitors/C(SMALL) | GRM1885C1H9R0DA01D | 0.1 | 0.2 | Digi-Key/Mouser
C2, C15, | 2 | 1uF | ted_capacitors/C(SMALL) | GRM188R61E105KA12D | 0.1 | 0.2 | Digi-Key
C4, C3, | 2 | 10pF | ted_capacitors/C(SMALL) | GRM1885C1H100FA01J | 0.12 | 0.24 | Mouser
C9, | 1 | 4.7uF | ted_capacitors/C(SMALL) | C0603C475K9PACTU | 0.13 | 0.13 | Mouser
FB1, | 1 | 500mA | ted_inductors/FERRITE_BEAD | MPZ2012S601A | 0.12 | 0.12 | Mouser
H1, H2, H4, H3, | 4 | HOLE | TED_holes/HOLE |  | 0 | 0
J1, | 1 | HEADER_6X1 | ted_connectors/HEADER_6X1 | 640456-6 | 0.27 | 0.27 | Mouser
J2, | 1 | JUMPER_2X1 | ted_connectors/JUMPER_2X1 | FCI 68000-102HLF | 0.19 | 0.19 | Digi-Key | AliExpress/Ebay
J3, J10, | 2 | Logic DC_2.1MM | ted_connectors/DC_2.1MM | Switchcraft RASM722X | 1.12 | 2.24 | Digi-Key/Mouser | AliExpress/Ebay
J7, J4, J5, | 3 | TERMINAL_8X1 | ted_connectors/TERMINAL_8X1 | 1814760 | 1.31 | 3.93 | Mouser
R12, R11, R10, R9, | 4 | 49.9 | ted_resistors/R_SMALL | ERJ-3EKF49R9V | 0.1 | 0.4 | Digi-Key
R14, | 1 | 4.7k | ted_resistors/R_SMALL | ERJ-3EKF4701V | 0.1 | 0.1 | Digi-Key
R15, R13, | 2 | 249 | ted_resistors/R_SMALL | ERJ-2RKF2490X | 0.1 | 0.2 | Digi-Key/Mouser
R16, | 1 | 10k 1% | ted_resistors/R_SMALL | ERJ-3EKF1001V | 0.1 | 0.1 | Digi-Key
R18, R19, R20, R17, R30, R31, R32, R29, R42, R43, R44, R41, | 12 | 10m | ted_resistors/R_SMALL | RL1220S-R10-F | 0.32 | 3.84 | Digi-Key
R26, R22, R27, R23, R28, R24, R25, R21, R38, R34, R39, R35, R40, R36, R37, R33,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 | 24 | 3.3k | ted_resistors/R_SMALL | ERJ-3EKF3301V | 0.1 | 2.4 | Digi-Key
R4, | 1 | 12.1k 1% | ted_resistors/R_SMALL | ERJ-6ENF1212V | 0.1 | 0.1 | Mouser
R5, | 1 | 10 | ted_resistors/R_SMALL | CRCW060310R0FKEA | 0.1 | 0.1 | Digi-Key/Mouser
R7, R6, R2, R1, R3, R8, | 6 | 33 | ted_resistors/R_SMALL | RC0603FR-0733RL | 0.1 | 0.6 | Digi-Key/Mouser
U1, | 1 | RJ45_12_PIN_SMD | ted_connectors/RJ45_12_PIN_SMD | HR961160C | 2.56 | 2.56 |  | AliExpress
U2, | 1 | LAN8720A | ted_ic/LAN8720A | LAN8720A | 1.49 | 1.49 | Digi-Key
U4, | 1 | PIC32MX664F128H | ted_ic/PIC32MX664F128H | PIC32MX664F128H-I/MR | 4.78 | 4.78 | MicrosoftDirect
U5, U6, U7, U3, U9, U10, U11, U8, U13, U14, U15, U12, | 12 | DRV8800_RTY | ted_ic/DRV8800_RTY | DRV8800RTYR | 2.38 | 28.56 | TI Store
X1, | 1 | 25Mhz | ted_crystals/CRYSTAL_W_2GND | FA-20H 25.0000MF20X-K3 | 0.73 | 0.73 | Mouser
X2, | 1 | 24MHz | ted_crystals/CRYSTAL_W_2GND | TSX-3225 24.0000MF20G-AC3 | 0.51 | 0.51 | Mouser
 |  |  |  |  |  | 64.05

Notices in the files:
projects/EthMotors_DRV8800_rev02/EthMotors_DRV8800_rev02_10x10.kicad_pcb:
GPL License
